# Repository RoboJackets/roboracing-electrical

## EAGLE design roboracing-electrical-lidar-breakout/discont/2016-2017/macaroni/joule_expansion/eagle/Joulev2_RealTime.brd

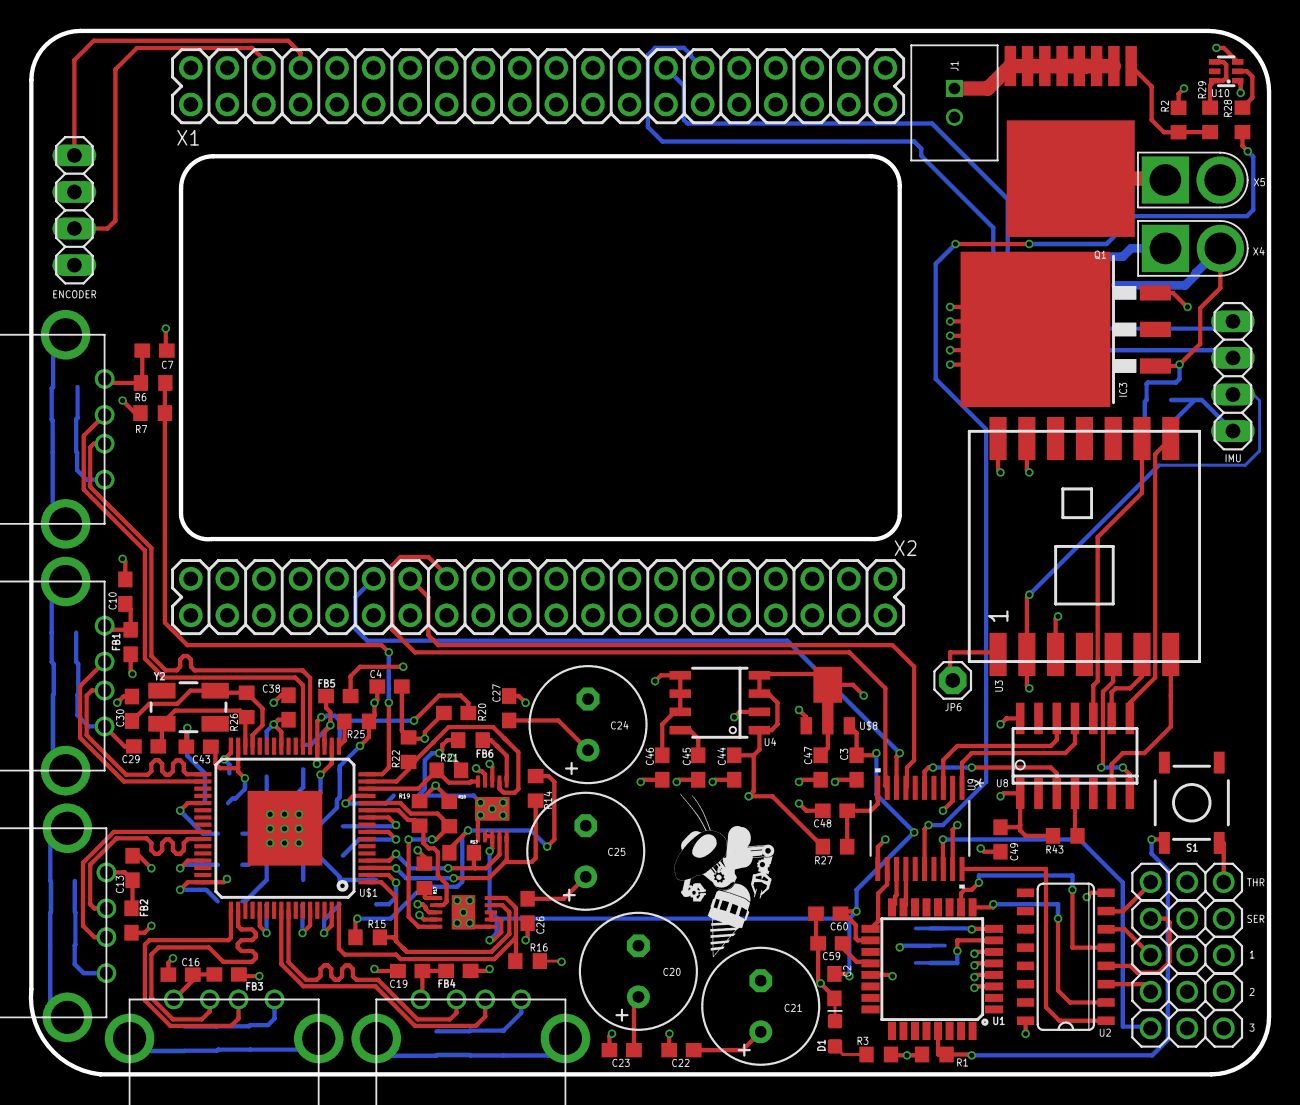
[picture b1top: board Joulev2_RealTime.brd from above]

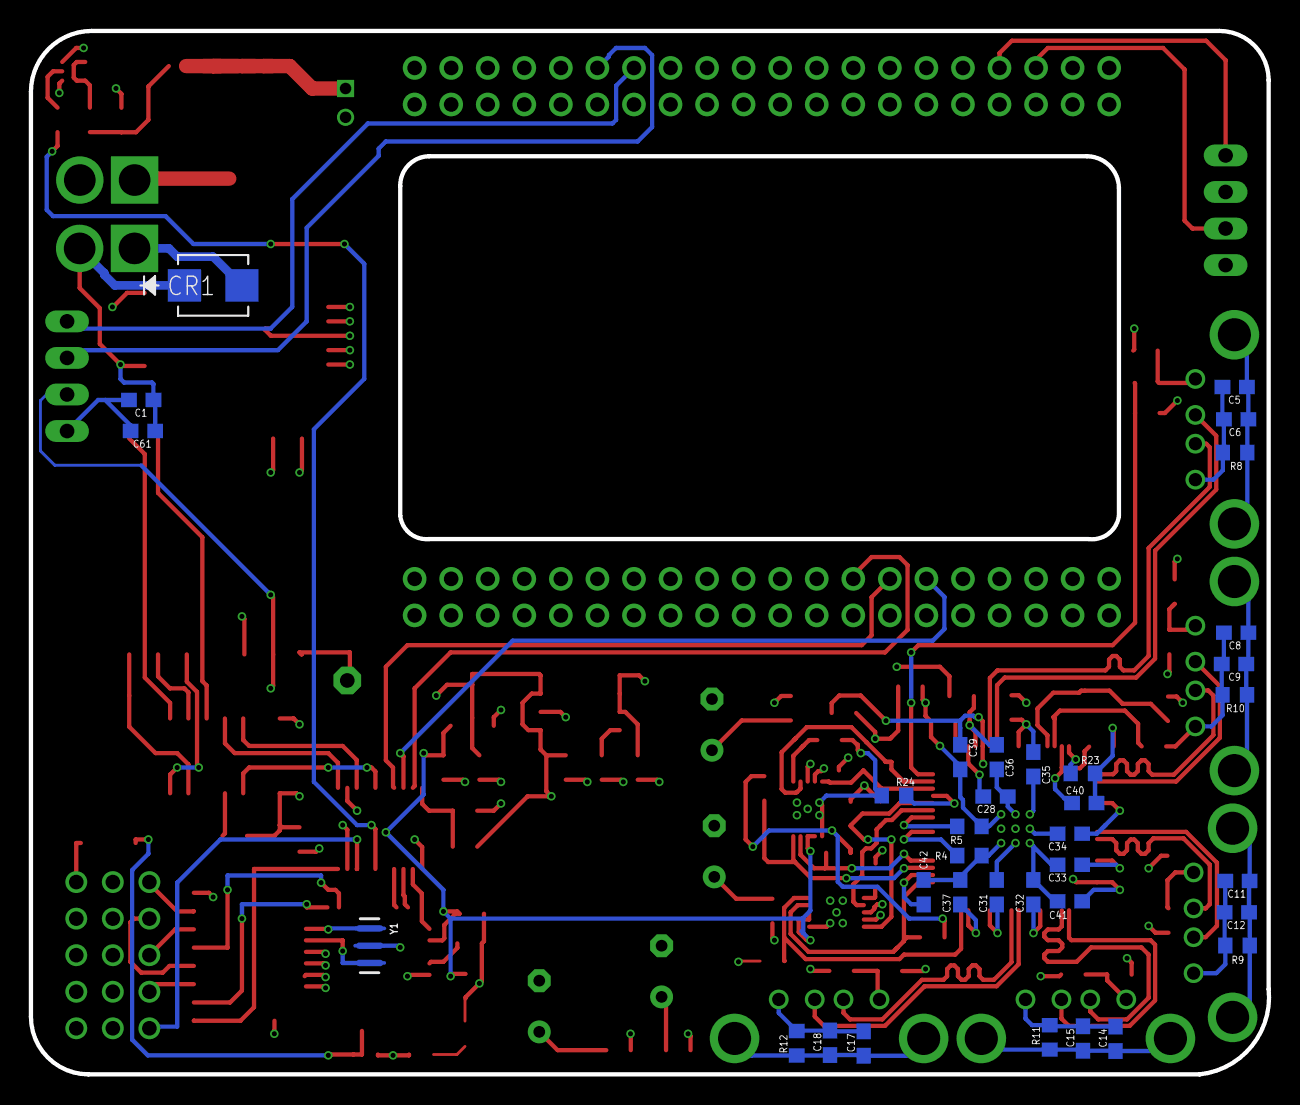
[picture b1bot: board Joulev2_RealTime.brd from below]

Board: 4 copper layers, 86.0 x 72.5 mm, 125 parts (35 on the bottom side), 94 nets.

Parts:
1, 2, 3: 1X03
C1: 0.22uF; C0603
C2, C5, C9, C10, C12, C13, C15, C16, C18, C19, C22, C23, C26, C27, C28, C31, C32, C33, C34, C35, C36, C37, C39, C40, C41, C42, C49, C59, C60: 0.1uF; C0603
C3, C4, C7, C38, C43, C61: 10uF; C0603
C6: 1.0nF; C0603
C8, C11, C14, C17: 1000pF; C0603
C20, C21, C24, C25: 150uF; E3,5-8
C29, C30: 18pF; C0603
C44, C46: 4.7uF; C0603
C45: 10000pF; C0603
C47: 22uF; C0603
C48: 1uF; C0603
CR1: SMBJ13CA; SMB
D1: LED-0603
ENCODER: 1X04
FB1, FB2, FB3, FB4, FB5, FB6: 220@100MHz; 0603
IC3: LM340S-05; TO263-3
IMU: 1X04
J1: 2-PIN_2MM-V; 2MM-2-V
JP6: antenna; 1X01
Q1: N_CH_MOSFET_FDLBL260N100; MO-299A
R1, R2, R7, R18, R19, R21, R22, R27, R43: 10k; R0603
R3: 680; R0603
R4, R5, R13, R14, R15, R16, R24, R25: 4.7k; R0603
R6: 90.9k; R0603
R8, R9, R10, R11, R12, R26: 1M; R0603
R17, R20: 25.5k; R0603
R23: 9.53k; R0603
R28: 500; R0603
R29: 10; R0603
S1: MOMENTARY-SWITCH 5.2mm; TACTILE_SWITCH_SMD_5.2MM
SER: 1X03
THR: 1X03
U1: ATMEGA328P_TQFP; TQFP32-08
U2: 74VHC_MUXSO16; SO16
U3: RFM69CW; RFM69CW-XXXS2
U4: ADP1706ARDZ-1.1-R7; SOIC8
U8: ATTINY441/841SSU/SSUR; SOIC-14
U9: TXB0108PWR; PW20
U10: ZXGD3009DY; SOT363
U$1: TUSB4041; TQFP64-10X10
U$3, U$4, U$5, U$6, U$7: USB_TYPE_A
U$8: AZ1117CR-3.3TRG1DICT-ND; SOT89R_INFINEON
U$9: ROBOBUZZ_0.6X
U$10, U$11: TPS2561DRCT; 10-VSON
X1: J12HEADER_(JOULE); 2X20
X2: J13HEADER_(JOULE); 2X20
X4, X5: TRAXXAS-CON
Y1: 16MHz; RESONATOR-SMD-3.2X1.3
Y2: 24MHz; CRYSTAL-SMD-5X3.2-4PAD

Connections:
1.1V: C46.1, FB5.2, U4.5, U4.6, U4.7
3.3V: C4.1, C44.1, C47.1, C49.1, FB6.2, IMU.2, R13.2, R14.2, R15.2, R16.2, R18.2, R19.2, R21.2, R22.2, R27.2, R43.2, U3.2, U4.1, U4.3, U4.4, U8.1, U9.2, U$8.2, U$8.4
5V: 1.2, 2.2, 3.2, C2.1, C3.1, C60.1, ENCODER.1, IC3.3, R1.1, R3.2, SER.2, THR.2, U1.4, U1.6, U1.18, U2.16, U9.19, U10.1, U$8.3, U$10.3, U$10.4, U$11.3, U$11.4
ACHANNEL_5V: ENCODER.2, X1.35
BCHANNEL_5V: ENCODER.4, X1.33
DIO0_3V3: U3.9, U8.10
DN1_VBUS: C24.+, C27.1, FB1.1, U$11.10
DN2_VBUS: C25.+, C26.1, FB2.1, U$11.9
DN3_VBUS: C20.+, C23.1, FB3.1, U$10.10
DN4_VBUS: C21.+, C22.1, FB4.1, U$10.9
ESTOP_3V3: U8.3, U9.5
ESTOP_5V: R28.1, U9.16
GND: 1.1, 2.1, 3.1, C1.2, C2.2, C3.2, C4.2, C5.2, C6.2, C7.2, C8.2, C9.2, C10.2, C11.2, C12.2, C13.2, C14.2, C15.2, C16.2, C17.2, C18.2, C19.2, C20.-, C21.-, C22.2, C23.2, C24.-, C25.-, C26.2, C27.2, C28.2, C29.2, C30.2, C31.2, C32.2, C33.2, C34.2, C35.2, C36.2, C37.2, C38.2, C39.2, C40.2, C41.2, C42.2, C43.2, C44.2, C45.2, C46.2, C47.2, C48.2, C49.2, C59.2, C60.2, C61.2, CR1.2, D1.C, ENCODER.3, IC3.TAB, IMU.1, J1.2, R2.2, R4.1, R5.1, R7.1, R8.1, R9.1, R10.1, R11.1, R12.1, R17.1, R20.1, R23.1, R24.1, R25.1, S1.3, SER.1, THR.1, U1.3, U1.5, U1.21, U2.8, U3.3, U3.13, U3.14, U4.2, U8.14, U9.11, U10.3, U$1.P$1, U$3.GND, U$4.GND, U$5.GND, U$6.GND, U$7.GND, U$8.1, U$10.1, U$10.2, U$11.1, U$11.2, X1.36, X1.37, X1.38, X1.39, X2.1, X2.3, X2.5, X2.7, X2.9, X4.GND, Y1.2
I2C0_SCL: IMU.4, X1.13
I2C0_SDA: IMU.3, X1.11
MISO_3V3: U3.8, U8.8
MISO_5V: U1.16, U9.13
MISO_JOULE: U9.8, X2.29
MODE_SELECT_3V3: U8.11, U9.1
MODE_SELECT_5V: U2.1, U9.20
MOSI_3V3: U3.5, U8.7
MOSI_5V: U1.15, U9.14
MOSI_JOULE: U9.7, X2.27
unnamed: JP6.1, U3.1
unnamed: SER.3, U2.4
unnamed: THR.3, U2.7
unnamed: R1.2, S1.1, U1.29
unnamed: Q1.DRAIN, X5.GND
unnamed: U1.7, Y1.1
unnamed: R28.2, U10.2
unnamed: U1.8, Y1.3
unnamed: R4.2, U$1.8
unnamed: 2.3, U2.3
unnamed: 1.3, U2.6
unnamed: R43.1, U8.4
unnamed: C59.1, U1.20
unnamed: R5.2, U$1.10
unnamed: R6.2, R7.2, U$1.16
unnamed: C7.1, R6.1, U$7.VBUS
unnamed: C13.1, FB2.2, U$4.VBUS
unnamed: C5.1, C6.1, R8.2, U$7.SHLD1, U$7.SHLD2
unnamed: U$1.22, U$7.DM
unnamed: D1.A, R3.1
unnamed: U$1.21, U$7.DP
unnamed: C16.1, FB3.2, U$5.VBUS
unnamed: C10.1, FB1.2, U$3.VBUS
unnamed: C19.1, FB4.2, U$6.VBUS
unnamed: R20.2, U$11.8
unnamed: C28.1, U$1.18
unnamed: R23.2, U$1.32
unnamed: R17.2, U$10.8
unnamed: C29.1, R26.1, U$1.30, Y2.1
unnamed: C30.1, R26.2, U$1.29, Y2.3
unnamed: R25.2, U$1.17
unnamed: C39.1, C40.1, C41.1, C42.1, C43.1, FB6.1, U$1.2, U$1.20, U$1.31, U$1.48
unnamed: R24.2, U$1.13
unnamed: C31.1, C32.1, C33.1, C34.1, C35.1, C36.1, C37.1, C38.1, FB5.1, U$1.19, U$1.25, U$1.37, U$1.45, U$1.53, U$1.60, U$1.63
unnamed: C17.1, C18.1, R12.2, U$6.SHLD1, U$6.SHLD2
unnamed: C14.1, C15.1, R11.2, U$5.SHLD1, U$5.SHLD2
unnamed: C8.1, C9.1, R10.2, U$3.SHLD1, U$3.SHLD2
unnamed: C11.1, C12.1, R9.2, U$4.SHLD1, U$4.SHLD2
unnamed: C45.1, U4.8
unnamed: C48.1, R27.1, U9.10
unnamed: R29.1, U10.4, U10.6
unnamed: J1.1, Q1.P2, Q1.P3, Q1.P4, Q1.P5, Q1.P6, Q1.P7, Q1.P8
unnamed: Q1.GATE, R2.1, R29.2
NSS_3V3: U3.7, U8.6
OVERCUR1Z: R21.1, U$1.14, U$11.11
OVERCUR2Z: R22.1, U$1.15, U$11.7
OVERCUR3Z: R18.1, U$1.12, U$10.11
OVERCUR4Z: R19.1, U$1.11, U$10.7
PC_PWM_SERVO: U1.9, U2.2
PC_PWM_THROTTLE: U1.10, U2.5
PWRCTL1: R13.1, U$1.4, U$11.5
PWRCTL2: R14.1, U$1.3, U$11.6
PWRCTL3: R15.1, U$1.1, U$10.5
PWRCTL4: R16.1, U$1.64, U$10.6
RC_CH3_3V3: U8.12, U9.3
RC_CH3_5V: 3.3, U9.18
SCK_3V3: U3.6, U8.9
SCK_5V: U1.17, U9.12
SCK_JOULE: U9.9, X2.25
USB_DM_DN1: U$1.34, U$3.DM
USB_DM_DN2: U$1.42, U$4.DM
USB_DM_DN3: U$1.50, U$5.DM
USB_DM_DN4: U$1.57, U$6.DM
USB_DP_DN1: U$1.33, U$3.DP
USB_DP_DN2: U$1.41, U$4.DP
USB_DP_DN3: U$1.49, U$5.DP
USB_DP_DN4: U$1.56, U$6.DP
V1P8V: X2.10, X2.12
V3P3V: X2.6, X2.8
V5P0V: X2.2, X2.4
VCC: C1.1, C61.1, CR1.1, IC3.1, X4.V+, X5.V+

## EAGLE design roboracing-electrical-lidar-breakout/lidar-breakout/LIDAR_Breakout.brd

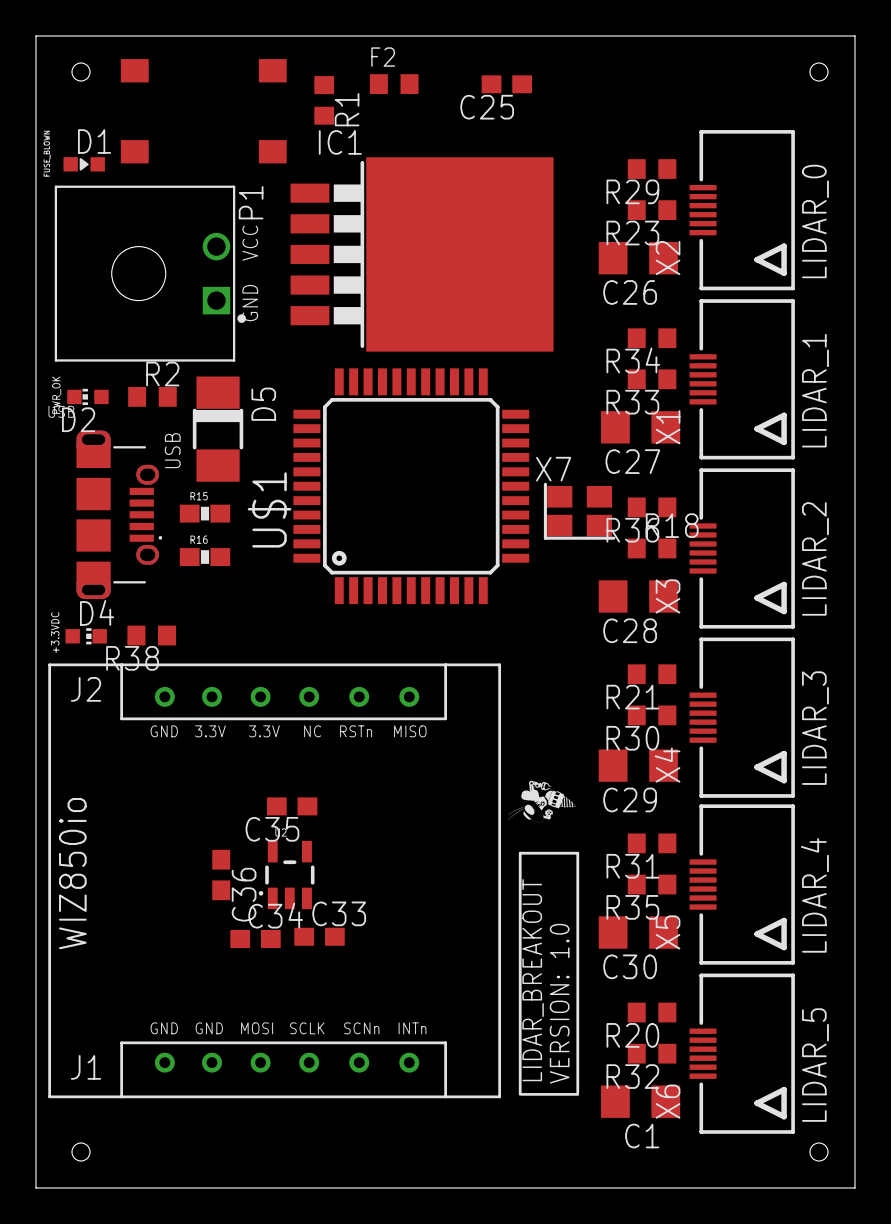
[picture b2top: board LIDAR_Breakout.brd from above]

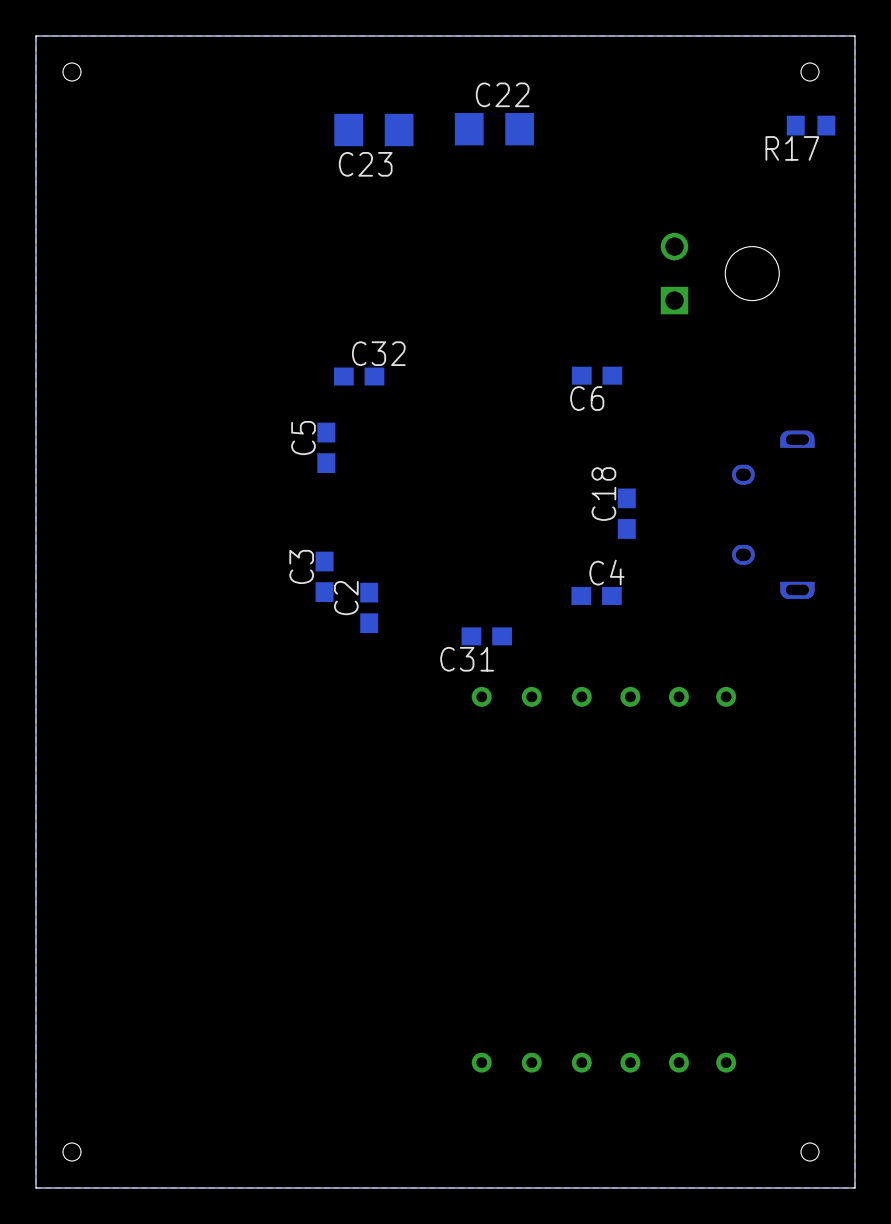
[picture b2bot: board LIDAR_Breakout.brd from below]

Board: 2 copper layers, 45.5 x 64.0 mm, 59 parts (11 on the bottom side), 33 nets, no tracks yet.

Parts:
C1, C26, C27, C28, C29, C30: 680 uF; C3216
C2, C4, C6, C25, C32, C36: 0.1 uF; C0603
C3, C5: 22 pF; C0603
C18: 10 nF; C0603
C22, C23: 10 uF; C3216
C31, C33: 1 uF; C0603
C34: 2.2 uF; C0603
C35: 470 pF; C0603
D1: LED-SMD-RED; CHIP-LED0603
D2, D4: GREEN; CHIP-LED0603
D5: DO-214AC
ETH_1: WIZ850IO
F2: 1.5 A; F0603
IC1: LP3852EMP-5.0; TO263-5
P1: 0436500200; MOLEX_0436500200
R1: 10k Ohm; R0603
R2, R17, R38: 1k Ohm; R0603
R15, R16: 22; 0603-RES
R18, R20, R21, R23, R29, R30, R31, R32, R33, R34, R35, R36: 4.7k; R0603
U2: MIC5219 3.3V; SOT23-5
U$1: ATMEGA32U4-AU; TQFP44
U$2: PTS645PTS645_SMD1; PTS645_SMD
U$3: ROBOBUZZ0.2X; ROBOBUZZ_0.2X
USB: MOLEX_47589-0001
X1, X2, X3, X4, X5, X6: 06FLZ-SM1; 6FLZ-SM
X7: XTAL-3.2X2.5

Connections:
+3.3V: C34.1, C36.1, ETH_1.8, ETH_1.9, R38.2, U2.5
D+: R15.1, U$1.4
D-: R16.1, U$1.3
GND: C1.2, C2.2, C3.2, C4.2, C5.2, C6.2, C18.2, C22.2, C23.2, C25.2, C26.2, C27.2, C28.2, C29.2, C30.2, C31.2, C32.2, C36.2, D2.C, D4.C, ETH_1.1, ETH_1.2, ETH_1.7, IC1.3, IC1.6, P1.1, U$1.5, U$1.15, U$1.23, U$1.35, U$1.43, U$2.P$3, U$2.P$4, USB.5, USB.P$1, USB.P$2, USB.P$3, USB.P$4, USB.P$5, USB.P$6, X1.6, X2.6, X3.6, X4.6, X5.6, X6.6
INTN: ETH_1.6, U$1.12
LDR0_SCK: U$1.41, X5.2
LDR1_SCK: U$1.40, X4.2
LDR2_SCK: U$1.39, X1.2
LDR3_SCK: U$1.38, X2.2
LDR4_SCK: U$1.37, X3.2
LDR5_SCK: U$1.36, X6.2
MISO: ETH_1.12, U$1.11
MOSI: ETH_1.3, U$1.10
unnamed: D5.A, USB.1
unnamed: C22.1, D1.A, F2.2, IC1.1, IC1.2
unnamed: D2.A, R2.1
unnamed: D4.A, R38.1
unnamed: D1.C, R17.2
unnamed: C18.1, U$1.42
unnamed: C31.1, U$1.6
unnamed: R16.2, USB.2
unnamed: R15.2, USB.3
unnamed: C35.1, U2.4
unnamed: C33.2, C34.2, C35.2, U2.2
RST: ETH_1.11, R1.2, U$1.13, U$2.P$1, U$2.P$2
SCL: R18.1, R23.1, R30.1, R32.1, R33.1, R35.1, U$1.18, X1.4, X2.4, X3.4, X4.4, X5.4, X6.4
SCLK: ETH_1.4, U$1.9
SCNN: ETH_1.5, U$1.8
SDA: R20.1, R21.1, R29.1, R31.1, R34.1, R36.1, U$1.19, X1.5, X2.5, X3.5, X4.5, X5.5, X6.5
UVCC: D5.C, F2.1, P1.2, R17.1, U$1.2, U$1.7
VCC: C1.1, C2.1, C4.1, C6.1, C23.1, C25.1, C26.1, C27.1, C28.1, C29.1, C30.1, C32.1, C33.1, IC1.4, R1.1, R2.2, R18.2, R20.2, R21.2, R23.2, R29.2, R30.2, R31.2, R32.2, R33.2, R34.2, R35.2, R36.2, U2.1, U2.3, U$1.14, U$1.24, U$1.34, U$1.44, X1.1, X2.1, X3.1, X4.1, X5.1, X6.1
XTAL1: C3.1, U$1.17, X7.1
XTAL2: C5.1, U$1.16, X7.3

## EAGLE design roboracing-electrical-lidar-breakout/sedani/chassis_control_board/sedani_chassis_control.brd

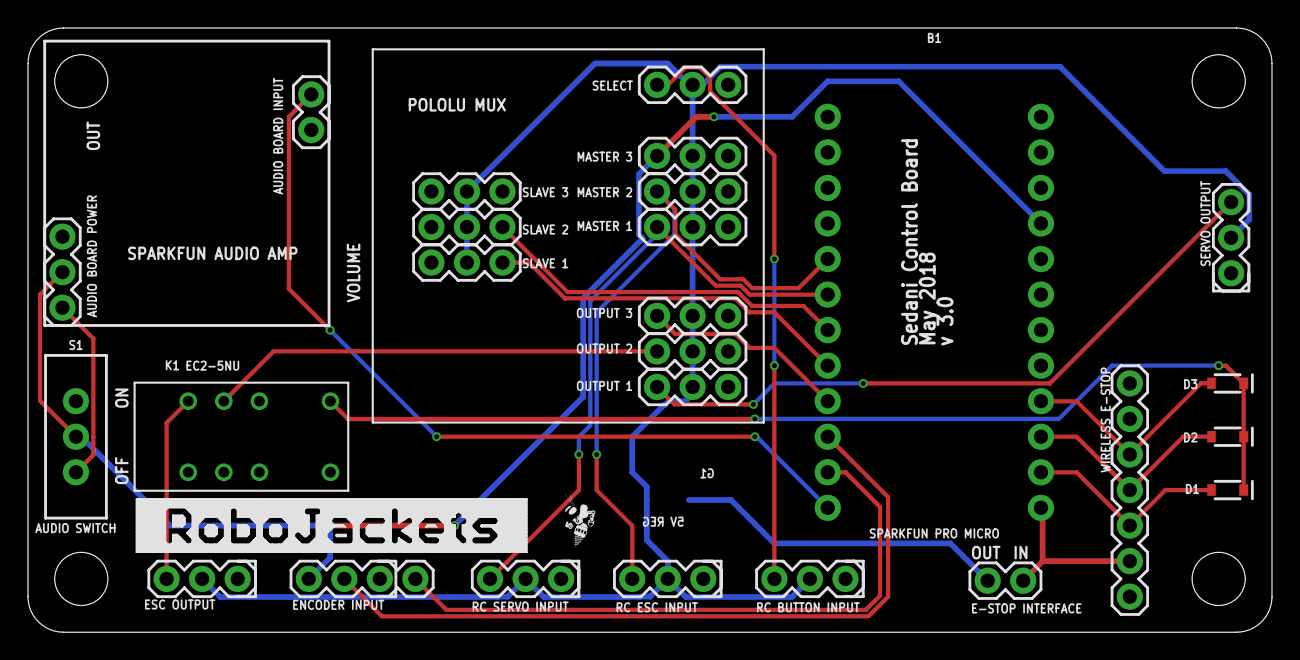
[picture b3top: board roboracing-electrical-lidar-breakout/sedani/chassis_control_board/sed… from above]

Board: 2 copper layers, 88.9 x 43.2 mm, 29 parts (1 on the bottom side), 22 nets.

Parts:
B1: SPARKFUN PRO MICRO; SPARKFUN_PRO_MICRO
D1, D2, D3: 250mA/100V; SOD-323
G1: 5V REG; SOT89
J1: WIRELESS E-STOP; 1X07
J2: E-STOP INTERFACE; 1X02
J3: MASTER 1; 1X03
J4: MASTER 2; 1X03
J5: MASTER 3; 1X03
J6: SLAVE 1; 1X03
J7: SLAVE 2; 1X03
J8: SLAVE 3; 1X03
J9: OUTPUT 1; 1X03
J10: OUTPUT 2; 1X03
J11: OUTPUT 3; 1X03
J12: SELECT; 1X03
J13: ENCODER INPUT; 1X04
J14: RC SERVO INPUT; 1X03
J15: RC ESC INPUT; 1X03
J16: RC BUTTON INPUT; 1X03
J17: AUDIO BOARD POWER; 1X03
J18: AUDIO BOARD INPUT; 1X02
J19: SERVO OUTPUT; 1X03
J20: ESC OUTPUT; 1X03
K1: EC2-5NU; EC2NU
S1: AUDIO SWITCH; SWITCH_SPDT_PTH_11.6X4.0MM
U$1: ROBOBUZZ_0.2X
U$2: ROBOJACKETS

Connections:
5V: B1.21, J5.3, J13.1, J17.2, S1.2
ARDUINO_ESC: B1.7, J7.3
ARDUINO_SERVO: B1.8, J6.3
ARD_SPEAKER_OUTPUT: B1.12, J18.1
E-STOP_INPUT: B1.13, J1.6, J2.1
E-STOP_OUTPUT: D1.C, D2.C, D3.C, K1.1
ENCODER_A: B1.10, J13.2
ENCODER_B: B1.11, J13.4
ESC_5V: G1.1, J2.2
GND: B1.3, B1.4, B1.23, G1.2, G1.2@1, J1.7, J3.1, J4.1, J5.1, J6.1, J7.1, J8.1, J8.3, J9.1, J10.1, J11.1, J12.1, J13.3, J14.1, J15.1, J16.1, J17.3, J18.2, J19.1, J20.1, K1.12
MUX_ESC: J10.3, K1.4
MUX_SEL_READ: B1.9, J11.3
OUT_ESC: J20.3, K1.5
OUT_SERVO: J9.3, J19.3
RC_BUTTON: J12.3, J16.3
RC_ESC: B1.5, J4.3, J15.3
RC_SERVO: B1.6, J3.3, J14.3
SPEAKER_DISABLE: J17.1, S1.3
VCC: G1.3, J3.2, J4.2, J5.2, J6.2, J7.2, J8.2, J9.2, J10.2, J11.2, J12.2, J14.2, J15.2, J16.2, J19.2, J20.2
WIRELESS_D0: B1.14, D1.A, J1.5
WIRELESS_D1: B1.15, D2.A, J1.4
WIRELESS_D2: B1.16, D3.A, J1.3

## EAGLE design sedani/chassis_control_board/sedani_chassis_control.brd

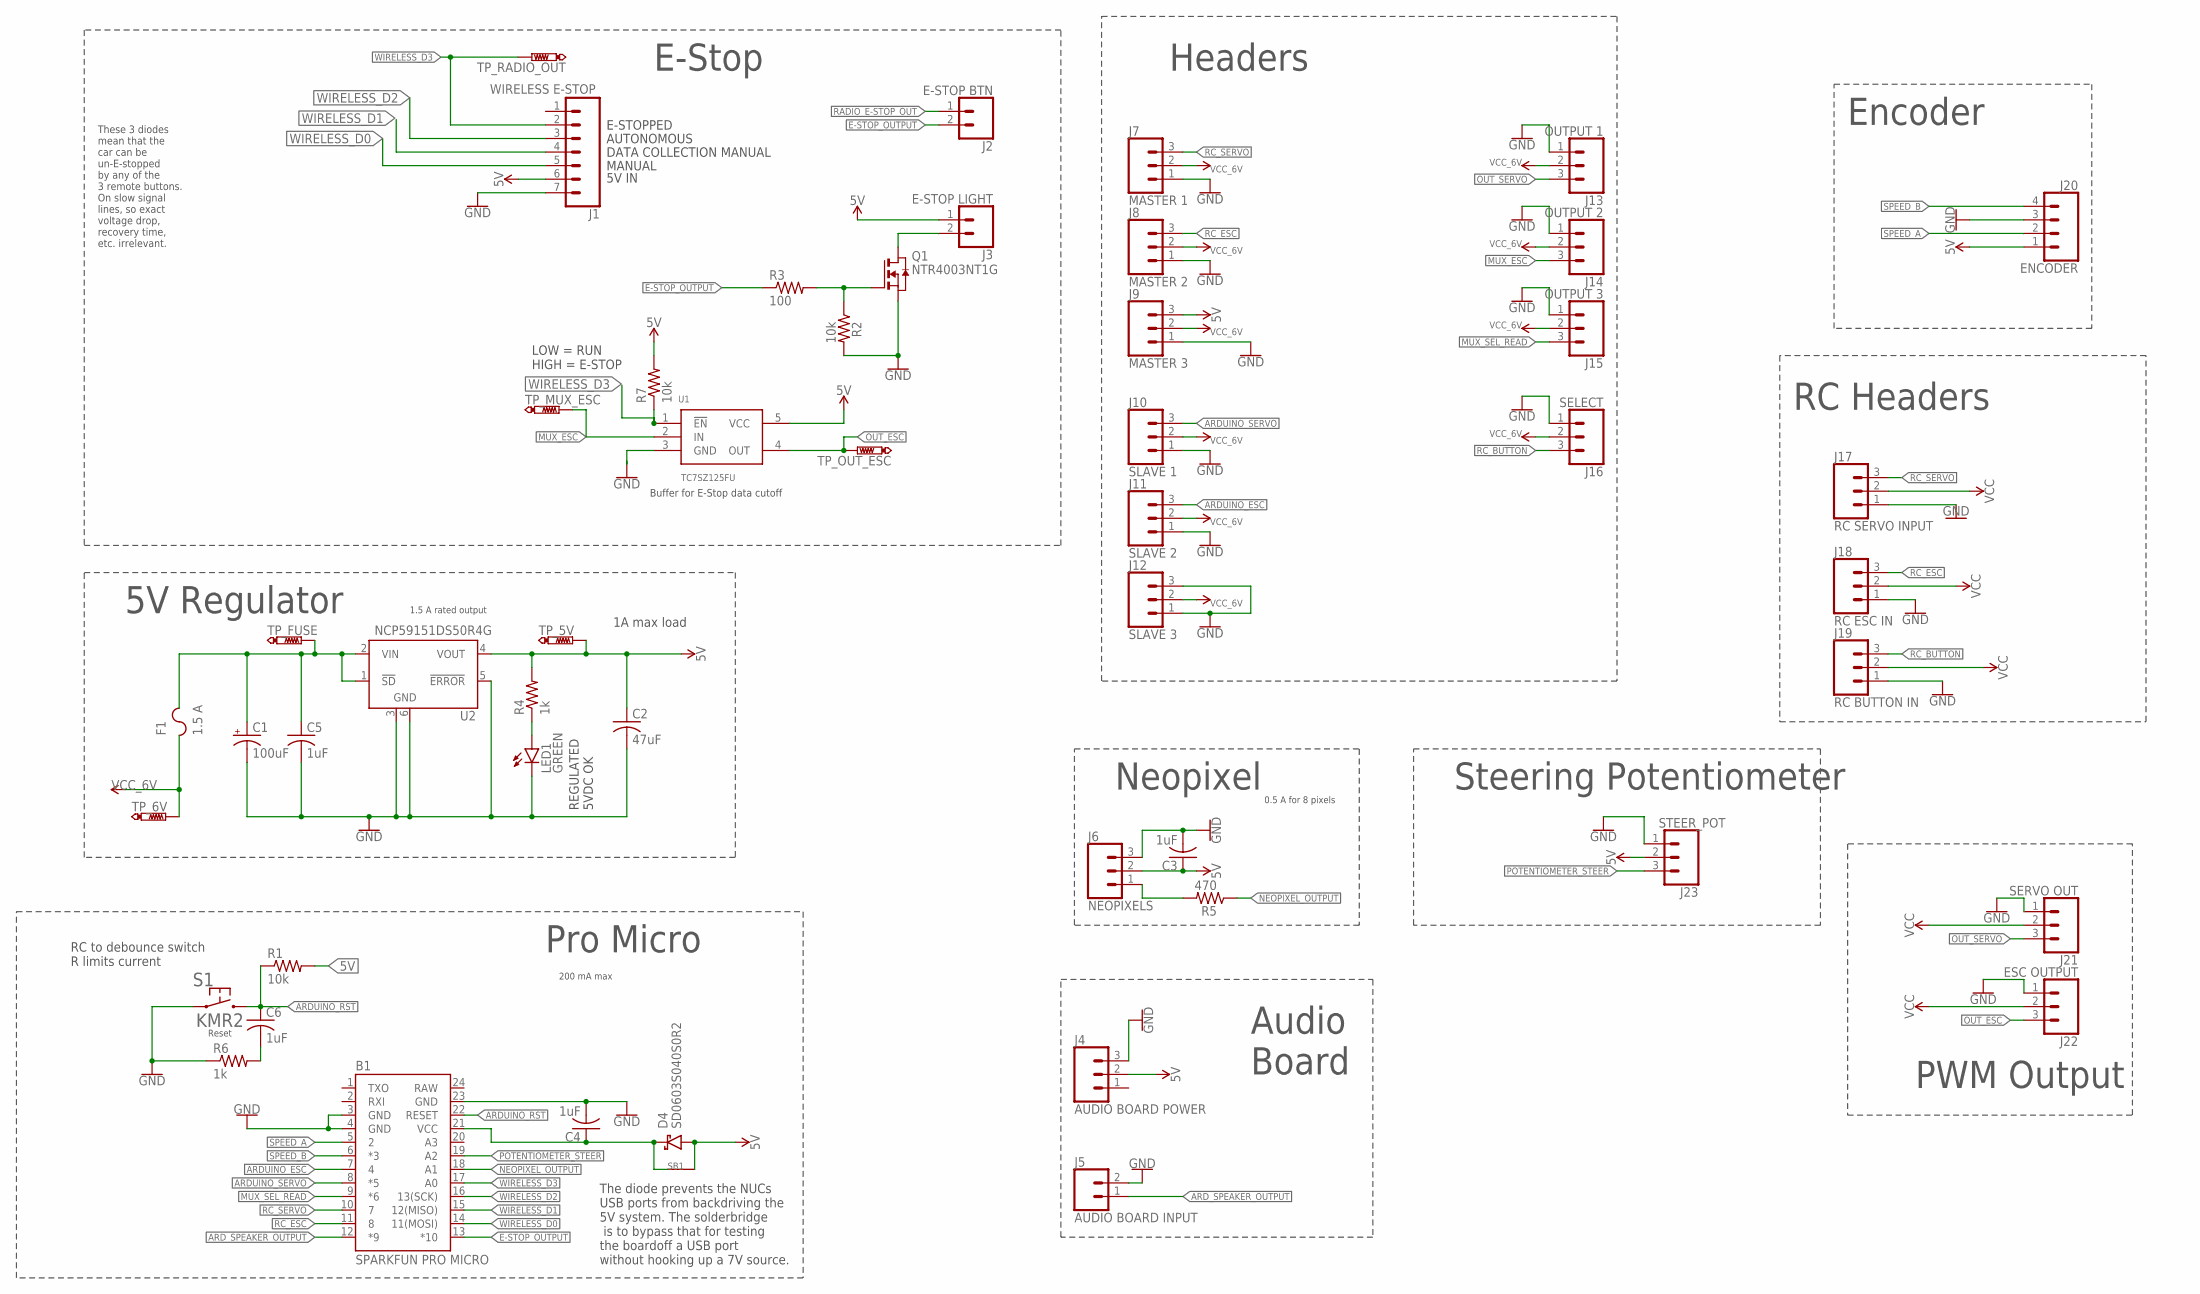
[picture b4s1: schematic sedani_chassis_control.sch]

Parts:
B1: SPARKFUN PRO MICRO; SPARKFUN_PRO_MICRO
C1: 100uF; E2-5
C2: 47uF; C1206
C3, C4, C5, C6: 1uF; C0603
D4: SD0603S040S0R2; SOD-323
F1: 1.5 A; F1812
J1: WIRELESS E-STOP; 1X07
J2: E-STOP BTN; 1X02
J3: E-STOP LIGHT; 1X02
J4: AUDIO BOARD POWER; 1X03
J5: AUDIO BOARD INPUT; 1X02
J6: NEOPIXELS; 1X03
J7: MASTER 1; 1X03
J8: MASTER 2; 1X03
J9: MASTER 3; 1X03
J10: SLAVE 1; 1X03
J11: SLAVE 2; 1X03
J12: SLAVE 3; 1X03
J13: OUTPUT 1; 1X03
J14: OUTPUT 2; 1X03
J15: OUTPUT 3; 1X03
J16: SELECT; 1X03
J17: RC SERVO INPUT; 1X03
J18: RC ESC IN; 1X03
J19: RC BUTTON IN; 1X03
J20: ENCODER; 1X04
J21: SERVO OUT; 1X03
J22: ESC OUTPUT; 1X03
J23: STEER_POT; 1X03
LED1: GREEN; CHIP-LED0603
Q1: NTR4003NT1G; SOT-23-3
R1, R2, R7: 10k; R0603
R3: 100; R0603
R4, R6: 1k; R0603
R5: 470; R0603
S1: KMR2
SB1: SOLDERBRIDGESB0603; SB0603
TP_5V, TP_6V: PTR1B1,27; B1,27
TP_FUSE: PTR1B1,27; B1,27
TP_MUX_ESC: PTR1B1,27; B1,27
TP_OUT_ESC: PTR1B1,27; B1,27
TP_RADIO_OUT: PTR1B1,27; B1,27
U1: TC7SZ125FU; SOT-353
U2: NCP59151DS50R4G; TO263-5

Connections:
5V: C2.1, C3.1, D4.A, J1.6, J3.1, J4.2, J6.2, J9.3, J20.1, J23.2, R1.2, R4.2, R7.2, SB1.2, TP_5V.TP, U1.5 (VCC), U2.4 (VOUT)
ARDUINO_ESC: B1.7 (4), J11.3
ARDUINO_RST: B1.22 (RESET), C6.1, R1.1, S1.2.1 (2), S1.2.2 (2)
ARDUINO_SERVO: B1.8 (*5), J10.3
ARD_SPEAKER_OUTPUT: B1.12 (*9), J5.1
E-STOP_OUTPUT: B1.13 (*10), J2.2, R3.1
GND: B1.3 (GND), B1.4 (GND), B1.23 (GND), C1.-, C2.2, C3.2, C4.2, C5.2, J1.7, J4.3, J5.2, J6.3, J7.1, J8.1, J9.1, J10.1, J11.1, J12.1, J12.3, J13.1, J14.1, J15.1, J16.1, J17.1, J18.1, J19.1, J20.3, J21.1, J22.1, J23.1, LED1.C, Q1.2 (S), R2.2, R6.1, S1.1.1 (1), S1.1.2 (1), U1.3 (GND), U2.3 (GND), U2.5 (!ERROR), U2.6 (GND)
MUX_ESC: J14.3, TP_MUX_ESC.TP, U1.2 (IN)
MUX_SEL_READ: B1.9 (*6), J15.3
unnamed: J3.2, Q1.3 (D)
unnamed: B1.21 (VCC), C4.1, D4.C, SB1.1
unnamed: LED1.A, R4.1
unnamed: J6.1, R5.2
unnamed: C6.2, R6.2
unnamed: Q1.1 (G), R2.1, R3.2
NEOPIXEL_OUTPUT: B1.18 (A1), R5.1
OUT_ESC: J22.3, TP_OUT_ESC.TP, U1.4 (OUT)
OUT_SERVO: J13.3, J21.3
POTENTIOMETER_STEER: B1.19 (A2), J23.3
RADIO_E-STOP_OUT: J2.1
RAW: B1.24 (RAW)
RC_BUTTON: J16.3, J19.3
RC_ESC: B1.11 (8), J8.3, J18.3
RC_SERVO: B1.10 (7), J7.3, J17.3
SPEED_A: B1.5 (2), J20.2
SPEED_B: B1.6 (*3), J20.4
VCC_6V: F1.1, J7.2, J8.2, J9.2, J10.2, J11.2, J12.2, J13.2, J14.2, J15.2, J16.2, J17.2, J18.2, J19.2, J21.2, J22.2, TP_6V.TP
VIN: C1.+, C5.1, F1.2, TP_FUSE.TP, U2.1 (!SD), U2.2 (VIN)
WIRELESS_D0: B1.14 (11(MOSI)), J1.5
WIRELESS_D1: B1.15 (12(MISO)), J1.4
WIRELESS_D2: B1.16 (13(SCK)), J1.3
WIRELESS_D3: B1.17 (A0), J1.2, R7.1, TP_RADIO_OUT.TP, U1.1 (!EN)

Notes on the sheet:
E-STOPPED
AUTONOMOUS
DATA COLLECTION MANUAL
MANUAL
5V IN
REGULATED 5VDC OK
E-Stop
Headers
Encoder
Audio Board
Pro Micro
PWM Output
5V Regulator
Neopixel
These 3 diodes mean that the car can be un-E-stopped by any of the 3 remote buttons. On slow signal lines, so exact voltage drop, recovery time, etc. irrelevant.
0.5 A for 8 pixels
200 mA max
1A max load
1.5 A rated output
RC Headers
RC to debounce switch R limits current
The diode prevents the NUCs USB ports from backdriving the 5V system. The solderbridge is to bypass that for testing the boardoff a USB port without hooking up a 7V source.
Buffer for E-Stop data cutoff
LOW = RUN HIGH = E-STOP
Steering Potentiometer

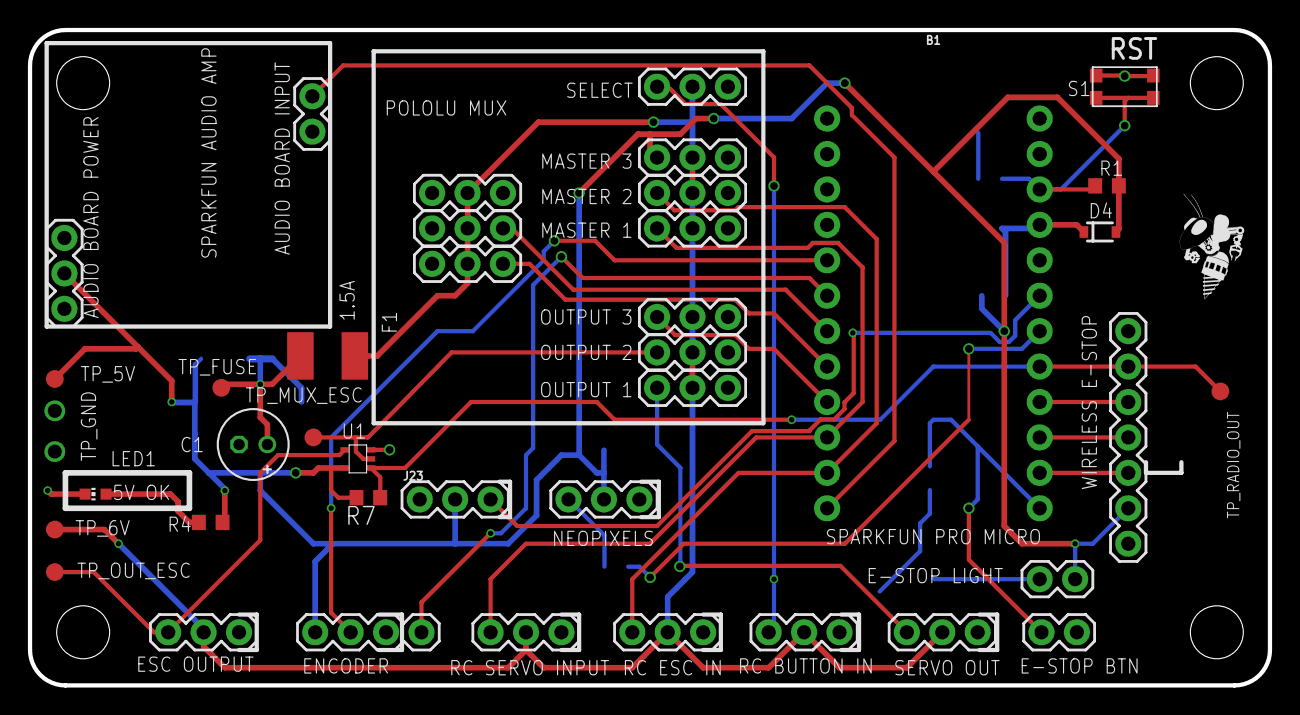
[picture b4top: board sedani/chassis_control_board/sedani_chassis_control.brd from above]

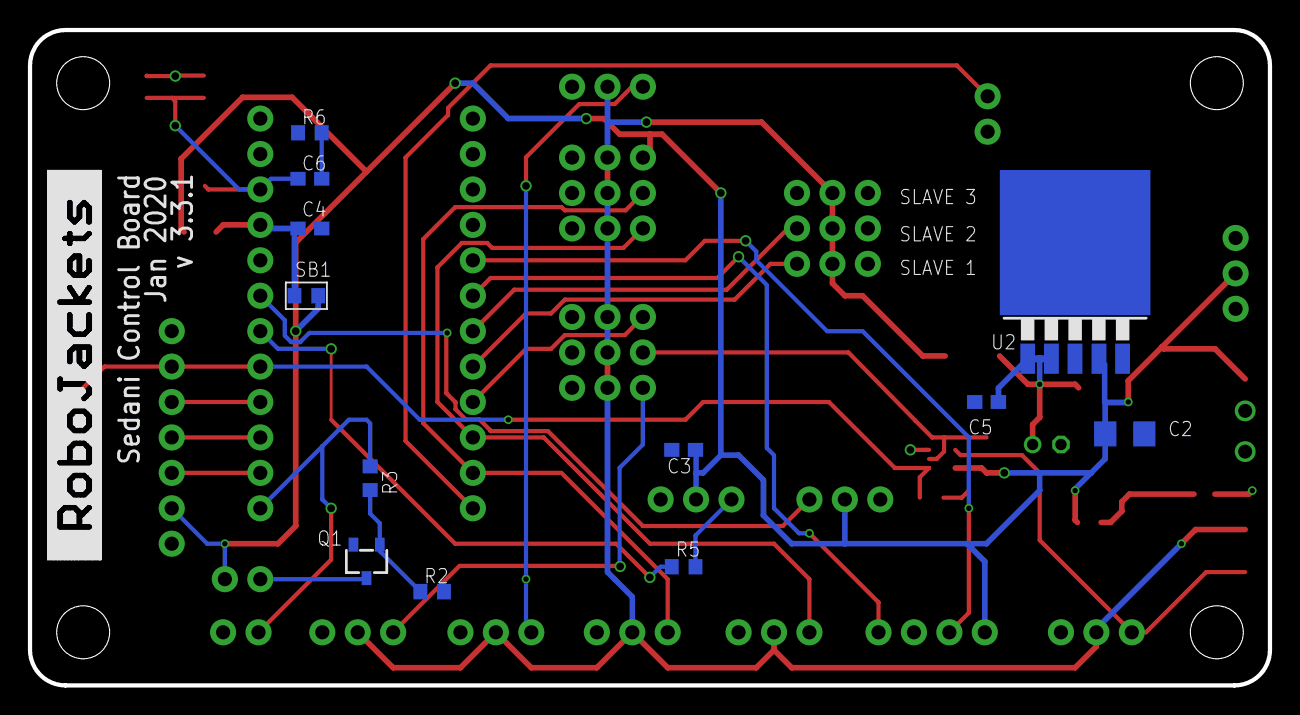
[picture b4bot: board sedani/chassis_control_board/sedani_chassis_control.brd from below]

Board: 2 copper layers, 88.9 x 47.0 mm, 53 parts (13 on the bottom side), 30 nets.

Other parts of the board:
U$2: ROBOJACKETS
U$3: ROBOBUZZ_0.4X

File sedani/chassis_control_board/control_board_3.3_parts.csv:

Part,Digikey Part Num,Description,,Unit Cost,Order,Total Cost,,
C1,732-8598-1-ND,100 uF Electrolytic Cap,,$0.10 ,2,$0.20 ,,
C2,587-1780-1-ND,47 uF Ceramic Cap,,$0.67 ,2,$1.40 ,,
"C3, C4, C5, C6",1276-1182-1-ND,1uF Ceramic Cap,,$0.10 ,6,$0.60 ,,
D4,478-7798-1-ND,Power diode,,$0.44 ,2,$0.88 ,,
F1,507-1773-1-ND,1.5 A fuse,,$0.21 ,2,$0.42 ,,
J1,S7005-ND,"1x7 Female 0.1"" Header",,$0.59 ,2,$1.18 ,,
"J2, J3, J5",S7000-ND,"1x2 Female 0.1"" Header",,$0.32 ,5,$1.60 ,,
"J4, J6, J7, J8, J9, J10, J11, J12, J13, J14, J15, J16, J17, J18, J19, J21, J22",S7001-ND,"1x3 Female 0.1"" Header",,$0.40 ,20,$8.00 ,,
J20,S7002-ND,"1x4 Female 0.1"" Header",,$0.45 ,2,$0.90 ,,
J22,732-5316-ND,"1x3 Male 0.1"" Header",,$0.13 ,2,$0.26 ,,
LED1,160-1446-1-ND,Green SMD LED,,$0.29 ,2,$0.58 ,,
Q1,NTR4003NT1GOSCT-ND,N MOSFET,,$0.30 ,2,$0.60 ,,
"R1, R2",TNP10.0KAACT-ND,10K 0603 Resistor,,$0.10 ,4,$0.40 ,,
R3,RR08P100DCT-ND,100 0603 Resistor,,$0.11 ,3,$0.33 ,,
"R4, R6",541-3991-1-ND,1K 0603 Resistor,,$0.03 ,10,$0.22 ,,
R5,A130089CT-ND,470 0603 Resistor,,$0.03 ,3,$0.08 ,,
S1,401-1426-1-ND,Reset Button,,$0.52 ,2,$1.04 ,,
U1,TC7SZ125FULJ(CTCT-ND,IC BUFFER NON-INVERT 5.5V USV,,$0.35 ,2,$0.70 ,,
U2,NCP59151DS50R4GOSCT-ND,Linear Voltage Regulator IC Positive Fixed 1 Output 1.5A,,$1.88 ,2,$3.76 ,,

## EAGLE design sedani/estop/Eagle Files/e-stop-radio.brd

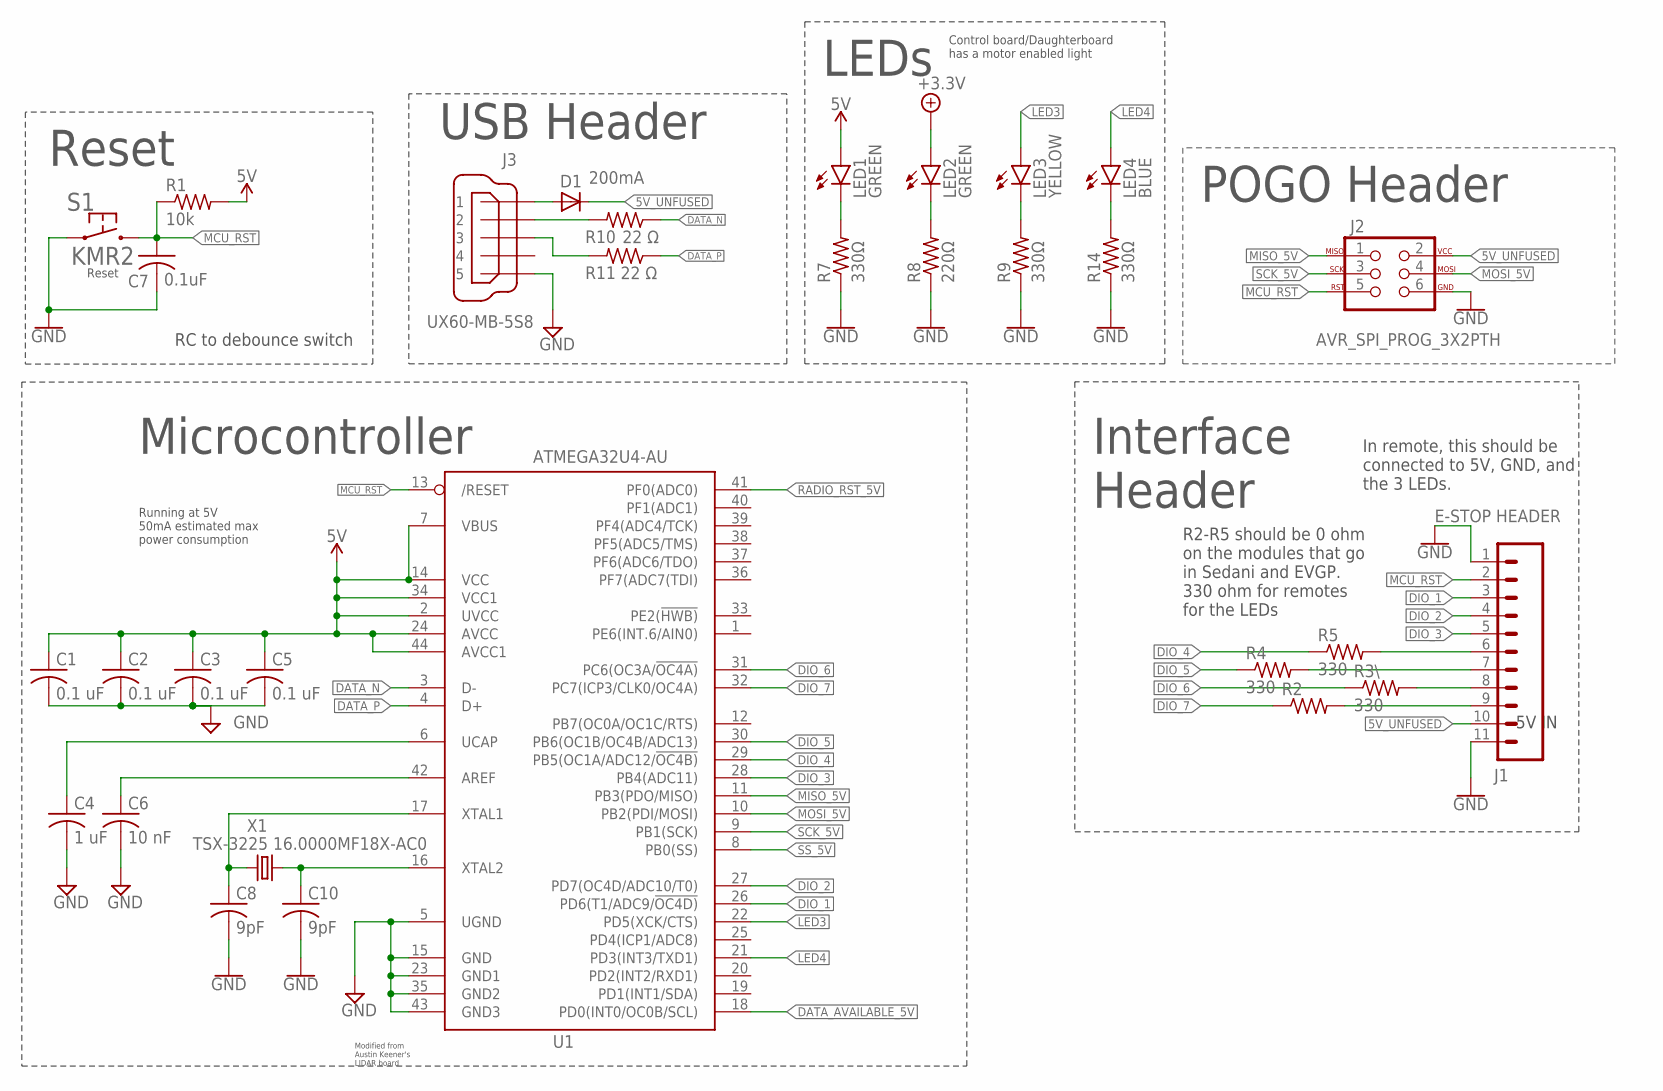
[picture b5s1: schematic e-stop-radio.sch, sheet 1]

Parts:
C1, C2, C3, C5: 0.1 uF; C0603
C4: 1 uF; C0603
C6: 10 nF; C0603
C7: 0.1uF; C0603
C8, C10: 9pF; C0603
D1: 200mA; SOD323-R
J1: E-STOP HEADER; 1X11
J2: AVR_SPI_PROG_3X2PTH; 2X3
J3: UX60-MB-5S8
LED1, LED2: GREEN; CHIP-LED0603
LED3: YELLOW; CHIP-LED0603
LED4: BLUE; CHIP-LED0603
R1: 10k; R0603
R2, R3\, R4, R5: 330; R0603
R7, R9, R14: 330Ω; R0603
R8: 220Ω; R0603
R10, R11: 22 Ω; R0603
S1: KMR2
U1: ATMEGA32U4-AU; TQFP44
X1: TSX-3225 16.0000MF18X-AC0; XTAL-3.2X2.5

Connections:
5V: C1.1, C2.1, C3.1, C5.1, LED1.A, R1.2, U1.2 (UVCC), U1.7 (VBUS), U1.14 (VCC), U1.24 (AVCC), U1.34 (VCC1), U1.44 (AVCC1); also elsewhere on the board
5V_UNFUSED: D1.C, J1.10, J2.2; also elsewhere on the board
+3.3V: LED2.A; also elsewhere on the board
AREF: C6.1, U1.42 (AREF)
DATA_AVAILABLE_5V: U1.18 (PD0(INT0/OC0B/SCL)); also elsewhere on the board
DATA_N: R10.1, U1.3 (D-)
DATA_P: R11.1, U1.4 (D+)
DIO_1: J1.3, U1.26 (PD6(T1/ADC9/!OC4D))
DIO_2: J1.4, U1.27 (PD7(OC4D/ADC10/T0))
DIO_3: J1.5, U1.28 (PB4(ADC11))
DIO_4: R5.1, U1.29 (PB5(OC1A/ADC12/!OC4B))
DIO_4_R: J1.6, R5.2
DIO_5: R4.1, U1.30 (PB6(OC1B/OC4B/ADC13))
DIO_5_R: J1.7, R4.2
DIO_6: R3\.1, U1.31 (PC6(OC3A/!OC4A))
DIO_6_R: J1.8, R3\.2
DIO_7: R2.1, U1.32 (PC7(ICP3/CLK0/OC4A))
DIO_7_R: J1.9, R2.2
GND: C1.2, C2.2, C3.2, C4.2, C5.2, C6.2, C7.2, C8.2, C10.2, J1.1, J1.11, J2.6, J3.5, R7.1, R8.1, R9.1, R14.1, S1.1.1 (1), S1.1.2 (1), U1.5 (UGND), U1.15 (GND), U1.23 (GND1), U1.35 (GND2), U1.43 (GND3); also elsewhere on the board
LED3: LED3.A, U1.22 (PD5(XCK/CTS))
LED4: LED4.A, U1.21 (PD3(INT3/TXD1))
MCU_RST: C7.1, J1.2, J2.5, R1.1, S1.2.1 (2), S1.2.2 (2), U1.13 (/RESET)
MISO_5V: J2.1, U1.11 (PB3(PDO/MISO)); also elsewhere on the board
MOSI_5V: J2.4, U1.10 (PB2(PDI/MOSI)); also elsewhere on the board
unnamed: LED3.C, R9.2
unnamed: LED1.C, R7.2
unnamed: LED2.C, R8.2
unnamed: J3.2, R10.2
unnamed: LED4.C, R14.2
unnamed: D1.A, J3.1
unnamed: J3.3, R11.2
RADIO_RST_5V: U1.41 (PF0(ADC0)); also elsewhere on the board
SCK_5V: J2.3, U1.9 (PB1(SCK)); also elsewhere on the board
SS_5V: U1.8 (PB0(SS)); also elsewhere on the board
UCAP: C4.1, U1.6 (UCAP)
XTAL1: C8.1, U1.17 (XTAL1), X1.1
XTAL2: C10.1, U1.16 (XTAL2), X1.3 (2)

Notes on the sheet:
Modified from Austin Keener's LIDAR board
5V IN
Interface Header
POGO Header
RC to debounce switch
Reset
Control board/Daughterboard has a motor enabled light
LEDs
Running at 5V 50mA estimated max power consumption
In remote, this should be connected to 5V, GND, and the 3 LEDs.
R2-R5 should be 0 ohm on the modules that go in Sedani and EVGP. 330 ohm for remotes for the LEDs
Microcontroller
USB Header

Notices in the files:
parts and their libraries:
SparkFun-Coils: Licensing: Creative Commons ShareAlike 4.0 International - https://creativecommons.org/licenses/by-sa/4.0
